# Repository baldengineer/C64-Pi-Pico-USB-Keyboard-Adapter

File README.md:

Here's a mirror for the [MT8816 Datasheet](https://bald.ee/mt8816).

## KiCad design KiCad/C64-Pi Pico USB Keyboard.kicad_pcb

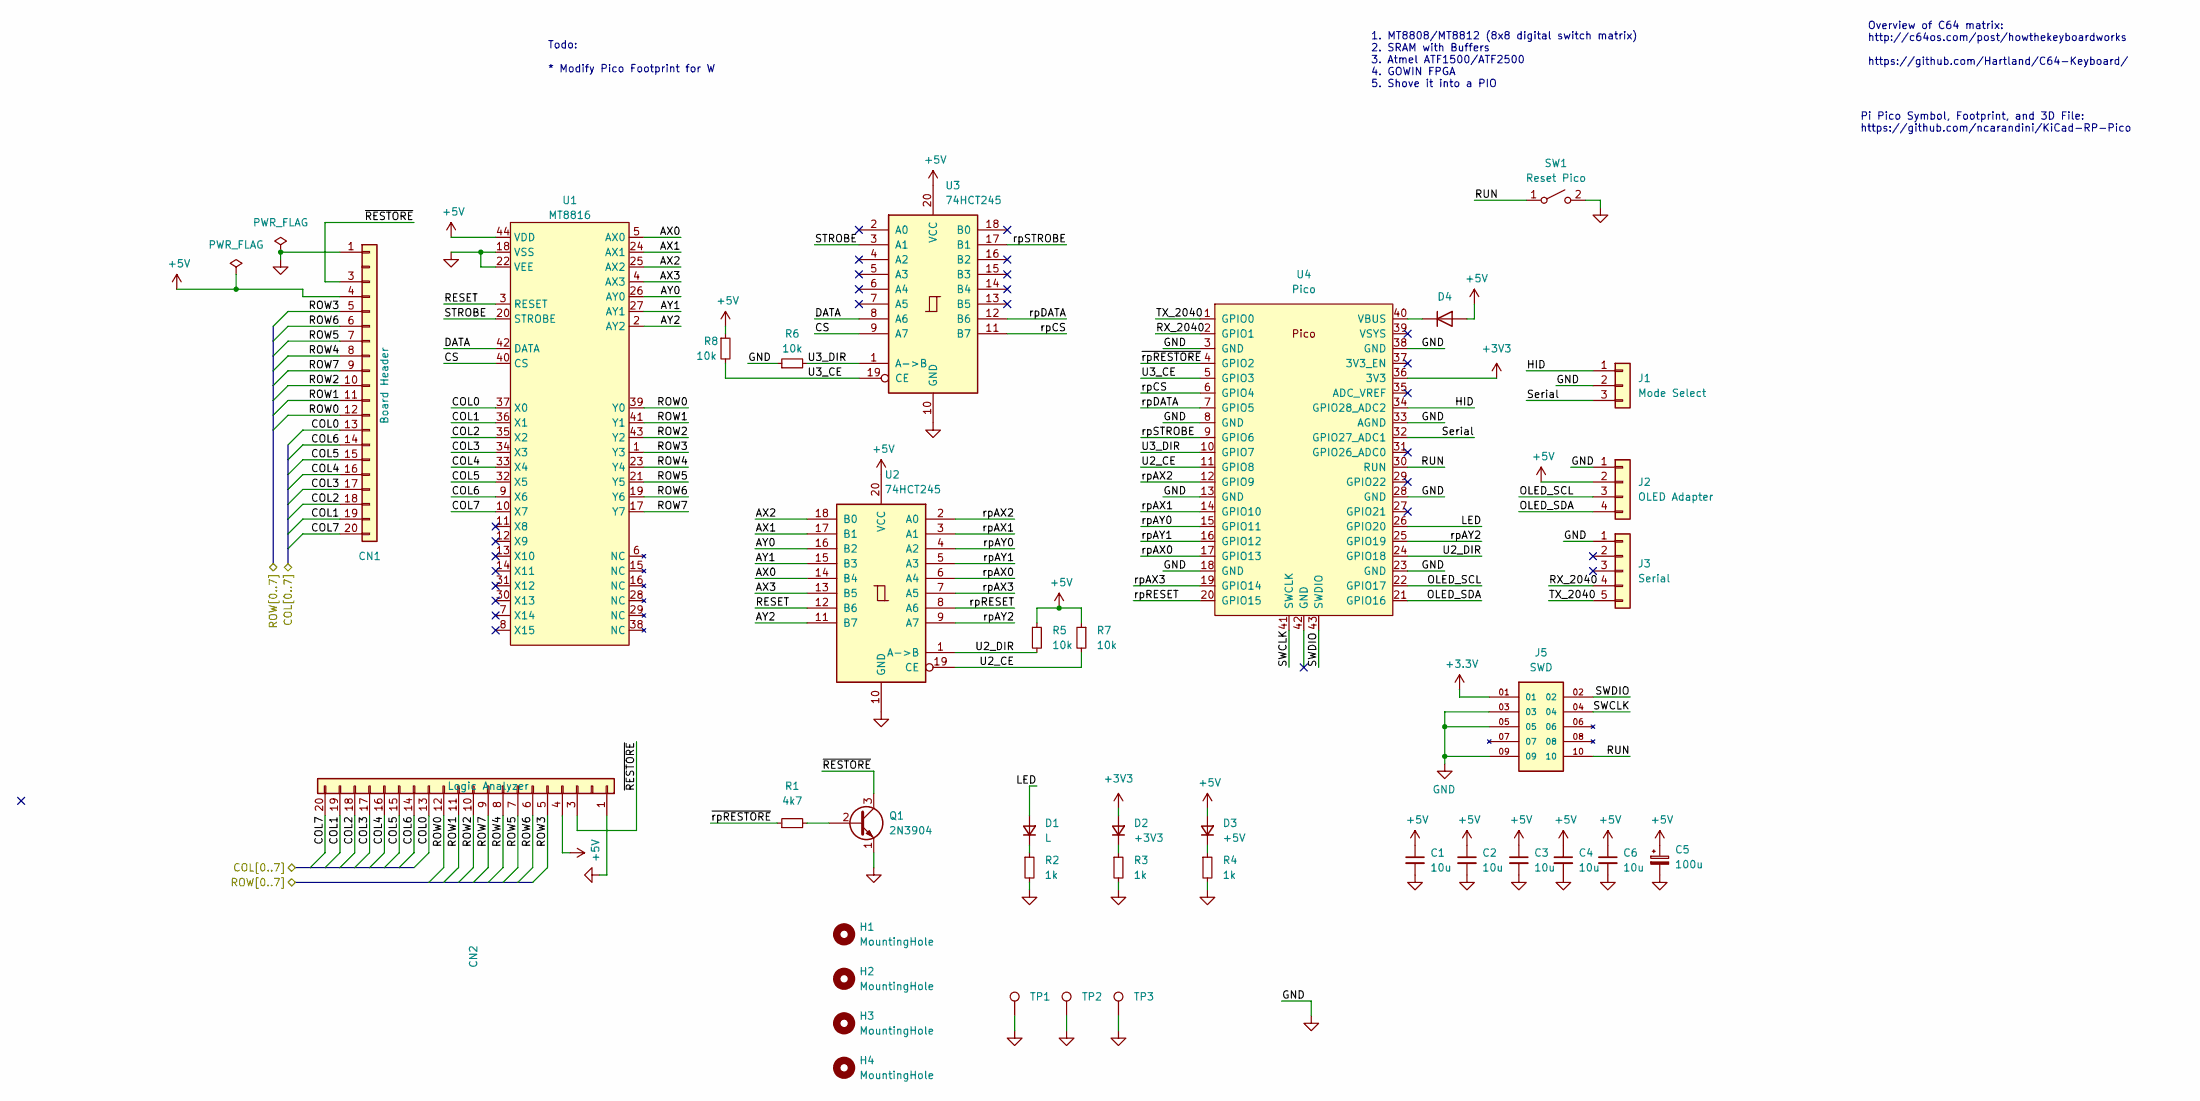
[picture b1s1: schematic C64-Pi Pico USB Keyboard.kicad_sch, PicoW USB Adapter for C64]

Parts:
C1, C2, C3, C4, C6: 10u; C_0805_2012Metric
C5: 100u; CP_Radial_D5.0mm_P2.50mm
CN1: Board Header; PinSocket_1x20_P2.54mm_Vertical
CN2: Logic Analyzer; PinHeader_1x20_P2.54mm_Vertical
D1: L; LED_1206_3216Metric
D2: +3V3; LED_1206_3216Metric
D3: +5V; LED_1206_3216Metric
D4: SM4001; D_SMA_Handsoldering
H1, H2, H3, H4: MountingHole; MountingHole_2.2mm_M2
J1: Mode Select; PinHeader_1x03_P2.54mm_Vertical
J2: OLED Adapter; PinSocket_1x04_P2.54mm_Vertical
J3: Serial; PinHeader_1x05_P2.54mm_Vertical
J5: SWD; SAMTEC_FTSH-105-XX-X-DV; PARTREV H
Q1: 2N3904; SOT-23
R1: 4k7; R_0805_2012Metric
R2, R3, R4: 1k; R_0805_2012Metric
R5, R6, R7, R8: 10k; R_0805_2012Metric
SW1: Reset Pico; SW_SPST_PTS810
TP1, TP2, TP3: TestPoint_Harwin; Harwin-S1751-46-Test-Point
U1: MT8816; PLCC-44_THT-Socket
U2, U3: 74HCT245; SOIC-20W_7.5x12.8mm_P1.27mm
U4: Pico; RPi_Pico_W_Combined_SMD_TH

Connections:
+5V: C1.1, C2.1, C3.1, C4.1, C5.1, C6.1, CN1.4, CN2.4, D3.2 (A), D4.2 (A), J2.2, R5.1, R7.1, R8.1, U1.44 (VDD), U2.20 (VCC), U3.20 (VCC)
/AX0: U1.5 (AX0), U2.14 (B4)
/AX1: U1.24 (AX1), U2.17 (B1)
/AX2: U1.25 (AX2), U2.18 (B0)
/AX3: U1.4 (AX3), U2.13 (B5)
/AY0: U1.26 (AY0), U2.16 (B2)
/AY1: U1.27 (AY1), U2.15 (B3)
/AY2: U1.2 (AY2), U2.11 (B7)
/COL0: CN1.13, CN2.13, U1.37 (X0)
/COL1: CN1.19, CN2.19, U1.36 (X1)
/COL2: CN1.18, CN2.18, U1.35 (X2)
/COL3: CN1.17, CN2.17, U1.34 (X3)
/COL4: CN1.16, CN2.16, U1.33 (X4)
/COL5: CN1.15, CN2.15, U1.32 (X5)
/COL6: CN1.14, CN2.14, U1.9 (X6)
/COL7: CN1.20, CN2.20, U1.10 (X7)
/CS: U1.40 (CS), U3.9 (A7)
/DATA: U1.42 (DATA), U3.8 (A6)
/HID: J1.1, U4.34 (GPIO28_ADC2)
/LED: D1.2 (A), U4.26 (GPIO20)
/OLED_SCL: J2.3, U4.22 (GPIO17)
/OLED_SDA: J2.4, U4.21 (GPIO16)
/RESET: U1.3 (RESET), U2.12 (B6)
/ROW0: CN1.12, CN2.12, U1.39 (Y0)
/ROW1: CN1.11, CN2.11, U1.41 (Y1)
/ROW2: CN1.10, CN2.10, U1.43 (Y2)
/ROW3: CN1.5, CN2.5, U1.1 (Y3)
/ROW4: CN1.8, CN2.8, U1.23 (Y4)
/ROW5: CN1.7, CN2.7, U1.21 (Y5)
/ROW6: CN1.6, CN2.6, U1.19 (Y6)
/ROW7: CN1.9, CN2.9, U1.17 (Y7)
/RUN: J5.10, SW1.1 (A), U4.30 (RUN)
/RX_2040: J3.4, U4.2 (GPIO1)
/STROBE: U1.20 (STROBE), U3.3 (A1)
/SWCLK: J5.04, U4.41 (SWCLK)
/SWDIO: J5.02, U4.43 (SWDIO)
/Serial: J1.3, U4.32 (GPIO27_ADC1)
/TX_2040: J3.5, U4.1 (GPIO0)
/U2_CE: R7.2, U2.19 (CE), U4.11 (GPIO8)
/U2_DIR: R5.2, U2.1 (A->B), U4.24 (GPIO18)
/U3_CE: R8.2, U3.19 (CE), U4.5 (GPIO3)
/U3_DIR: R6.2, U3.1 (A->B), U4.10 (GPIO7)
/rpAX0: U2.6 (A4), U4.17 (GPIO13)
/rpAX1: U2.3 (A1), U4.14 (GPIO10)
/rpAX2: U2.2 (A0), U4.12 (GPIO9)
/rpAX3: U2.7 (A5), U4.19 (GPIO14)
/rpAY0: U2.4 (A2), U4.15 (GPIO11)
/rpAY1: U2.5 (A3), U4.16 (GPIO12)
/rpAY2: U2.9 (A7), U4.25 (GPIO19)
/rpCS: U3.11 (B7), U4.6 (GPIO4)
/rpDATA: U3.12 (B6), U4.7 (GPIO5)
/rpRESET: U2.8 (A6), U4.20 (GPIO15)
/rpSTROBE: U3.17 (B1), U4.9 (GPIO6)
/~RESTORE: CN1.3, CN2.3, Q1.3 (C)
/~rpRESTORE: R1.1, U4.4 (GPIO2)
GND: C1.2, C2.2, C3.2, C4.2, C5.2, C6.2, CN1.1, CN2.1, J1.2, J2.1, J3.1, J5.03, J5.05, J5.09, Q1.1 (E), R2.2, R3.2, R4.2, R6.1, SW1.2 (B), TP1.1, TP2.1, TP3.1, U1.18 (VSS), U1.22 (VEE), U2.10 (GND), U3.10 (GND), U4.3 (GND), U4.8 (GND), U4.13 (GND), U4.18 (GND), U4.23 (GND), U4.28 (GND), U4.33 (AGND), U4.38 (GND)
unnamed: D1.1 (K), R2.1
unnamed: D2.1 (K), R3.1
unnamed: D3.1 (K), R4.1
unnamed: D4.1 (K), U4.40 (VBUS)
unnamed: Q1.2 (B), R1.2

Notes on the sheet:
Pi Pico Symbol, Footprint, and 3D File: https://github.com/ncarandini/KiCad-RP-Pico
Todo: * Modify Pico Footprint for W
Overview of C64 matrix: http://c64os.com/post/howthekeyboardworks https://github.com/Hartland/C64-Keyboard/
1. MT8808/MT8812 (8x8 digital switch matrix) 2. SRAM with Buffers 3. Atmel ATF1500/ATF2500 4. GOWIN FPGA 5. Shove it into a PIO

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
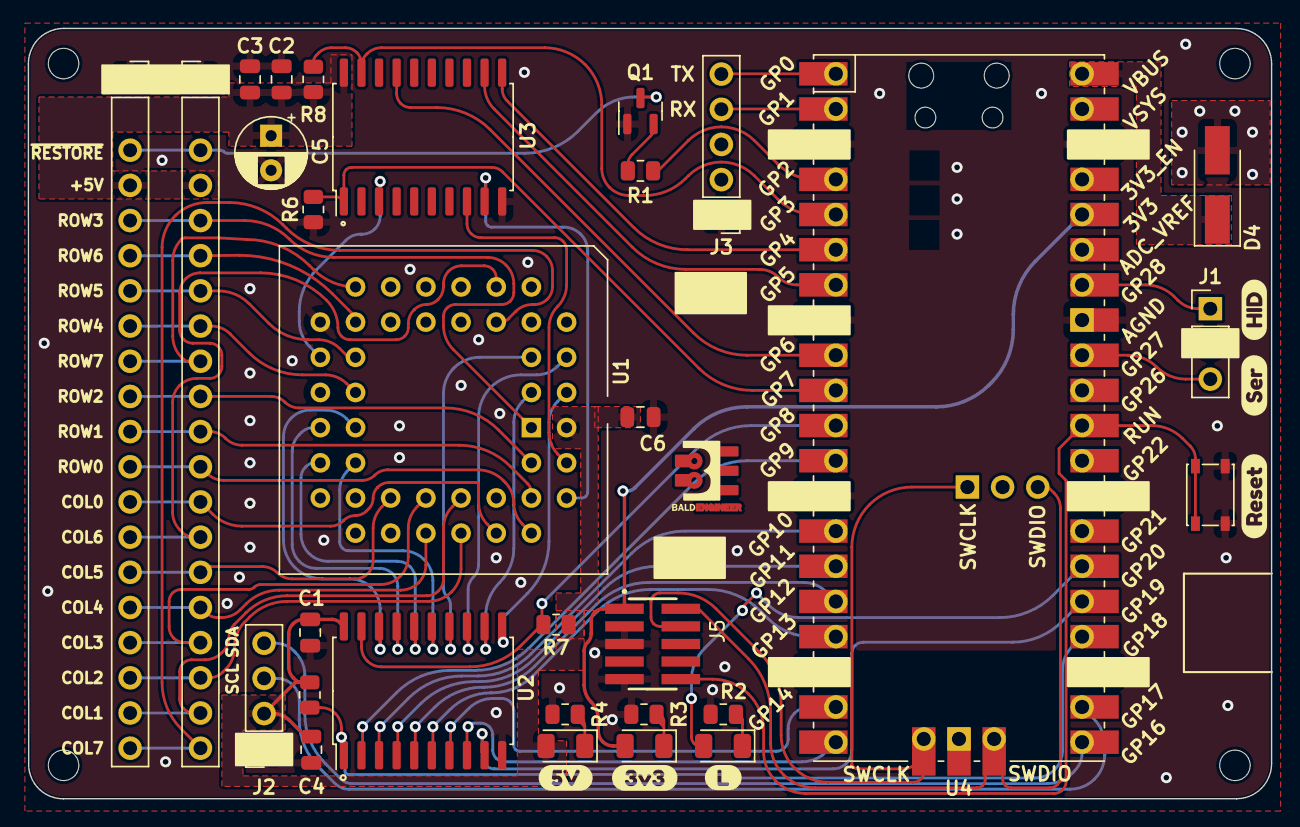
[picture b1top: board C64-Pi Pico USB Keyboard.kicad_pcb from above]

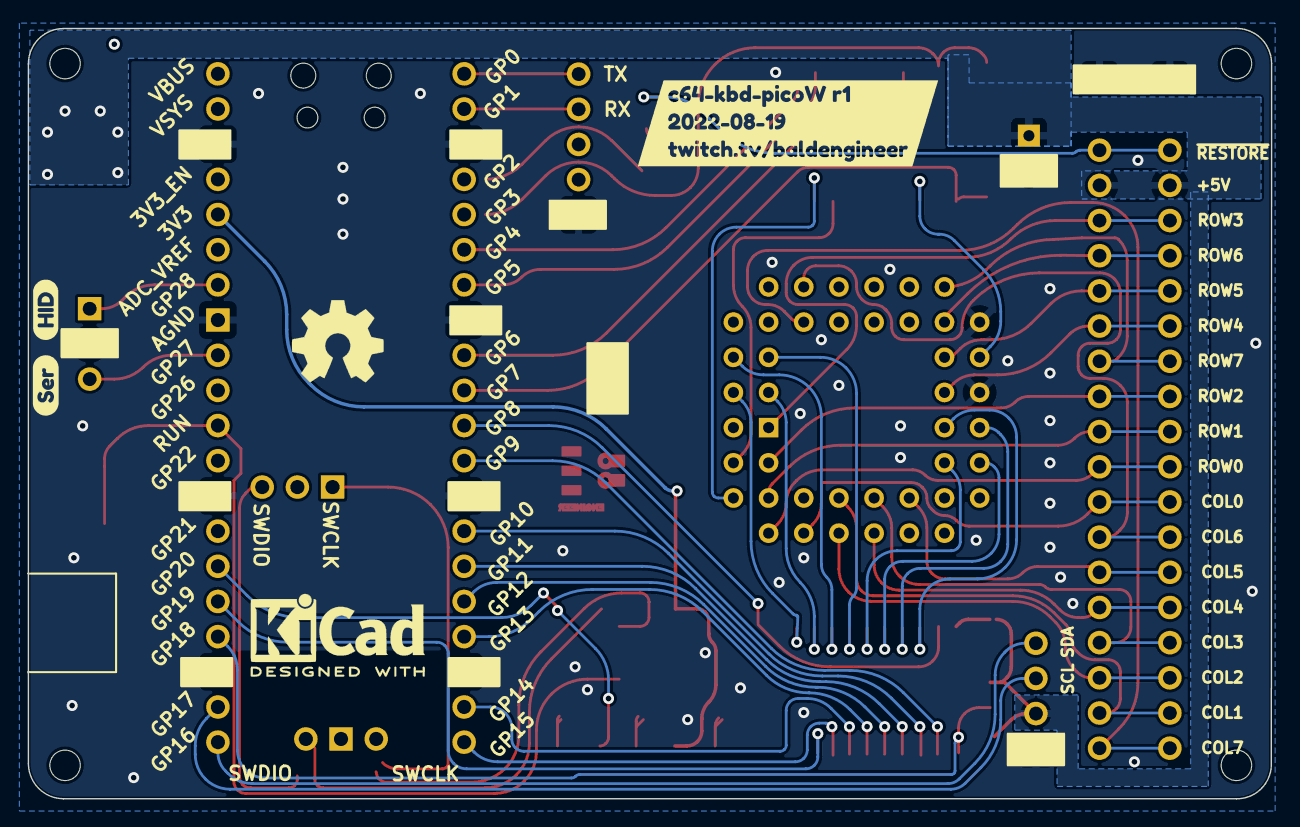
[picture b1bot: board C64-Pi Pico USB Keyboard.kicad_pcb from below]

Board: 2 copper layers, 89.8 x 55.6 mm, 47 parts (4 on the bottom side), 62 nets.

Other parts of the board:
kibuzzard-62FFC0C4: G***; kibuzzard-62FFC0C4
kibuzzard-62FFC0CE: G***; kibuzzard-62FFC0CE
kibuzzard-62FFC8C1: G***; kibuzzard-62FFC8C1
kibuzzard-62FFC8D3, kibuzzard-62FFC8D3#2: G***; kibuzzard-62FFC8D3
kibuzzard-62FFC8F9, kibuzzard-62FFC8F9#2: G***; kibuzzard-62FFC8F9
kibuzzard-62FFC032: G***; kibuzzard-62FFC032
kibuzzard-62FFC121: G***; kibuzzard-62FFC121
svg2mod: G***; BE5v2

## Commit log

2022-09-05 Update README.md
    added URL for datasheet
2022-09-05 Fixed MT8816 timing!
2022-09-09 basic keys working
2022-09-10 Mapped most C64 alpha and shifted keys. Ctrl also working.
